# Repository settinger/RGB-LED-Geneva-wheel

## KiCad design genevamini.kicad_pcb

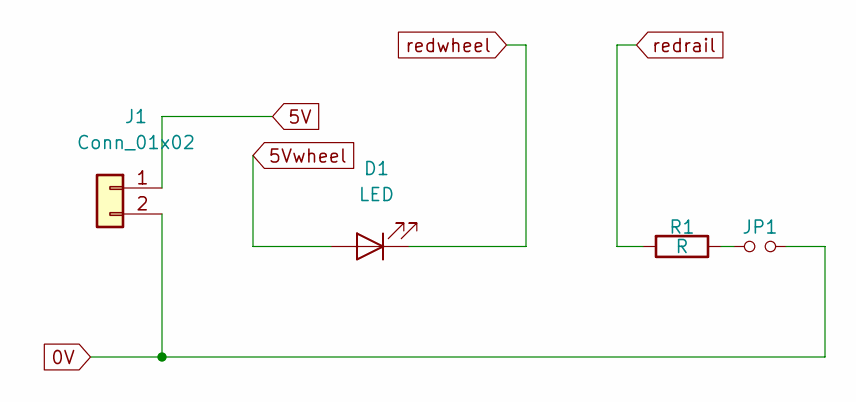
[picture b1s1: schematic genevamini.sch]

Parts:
D1: LED; LED_D3.0mm
J1: Conn_01x02; BatteryHolder_Keystone_1058_1x2032
JP1: Jumper_NO_Small; jumper
R1: R; R_Axial_DIN0204_L3.6mm_D1.6mm_P7.62mm_Horizontal

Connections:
0V: J1.2, JP1.2
5V: J1.1
5Vwheel: D1.2 (A)
unnamed: JP1.1, R1.1
redrail: R1.2
redwheel: D1.1 (K)

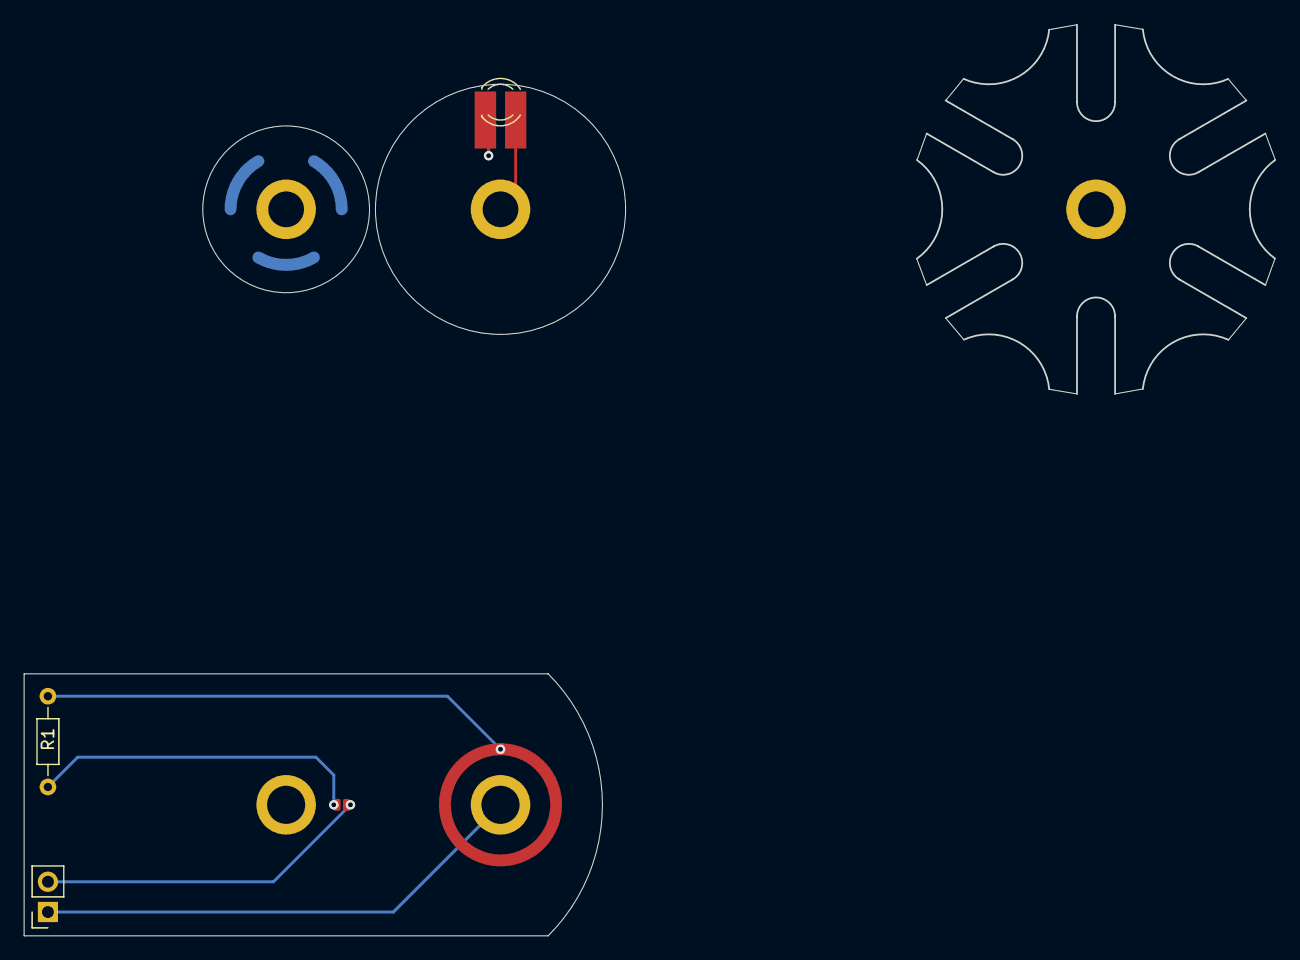
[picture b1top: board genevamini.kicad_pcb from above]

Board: 2 copper layers, 105.1 x 76.5 mm, 4 parts (0 on the bottom side), 2 nets.

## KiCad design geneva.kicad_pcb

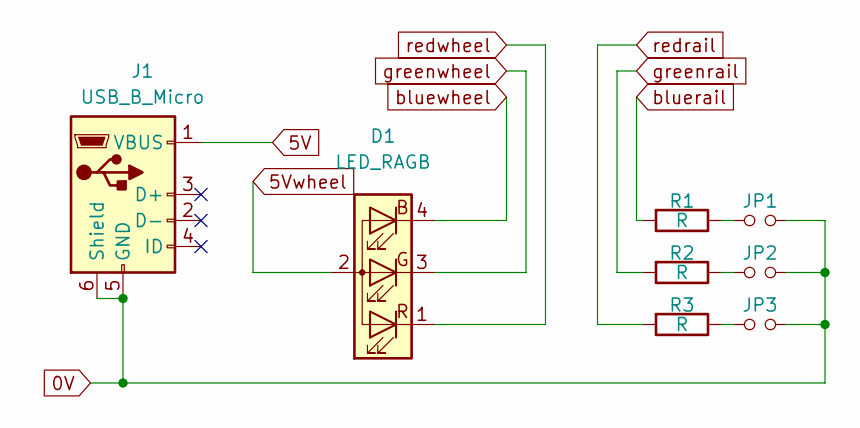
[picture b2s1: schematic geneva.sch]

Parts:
D1: LED_RAGB; LED_D5.0mm-4_RGB
J1: USB_B_Micro; USB_Micro-B_GCT_USB3076-30-A
JP1, JP2, JP3: Jumper_NO_Small; jumper
R1, R2, R3: R; R_Axial_DIN0204_L3.6mm_D1.6mm_P7.62mm_Horizontal

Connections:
0V: J1.5 (GND), J1.6 (Shield), JP1.2, JP2.2, JP3.2
5V: J1.1 (VBUS)
5Vwheel: D1.2 (A)
unnamed: JP1.1, R1.1
unnamed: JP2.1, R2.1
unnamed: JP3.1, R3.1
bluerail: R1.2
bluewheel: D1.4 (BK)
greenrail: R2.2
greenwheel: D1.3 (GK)
redrail: R3.2
redwheel: D1.1 (RK)

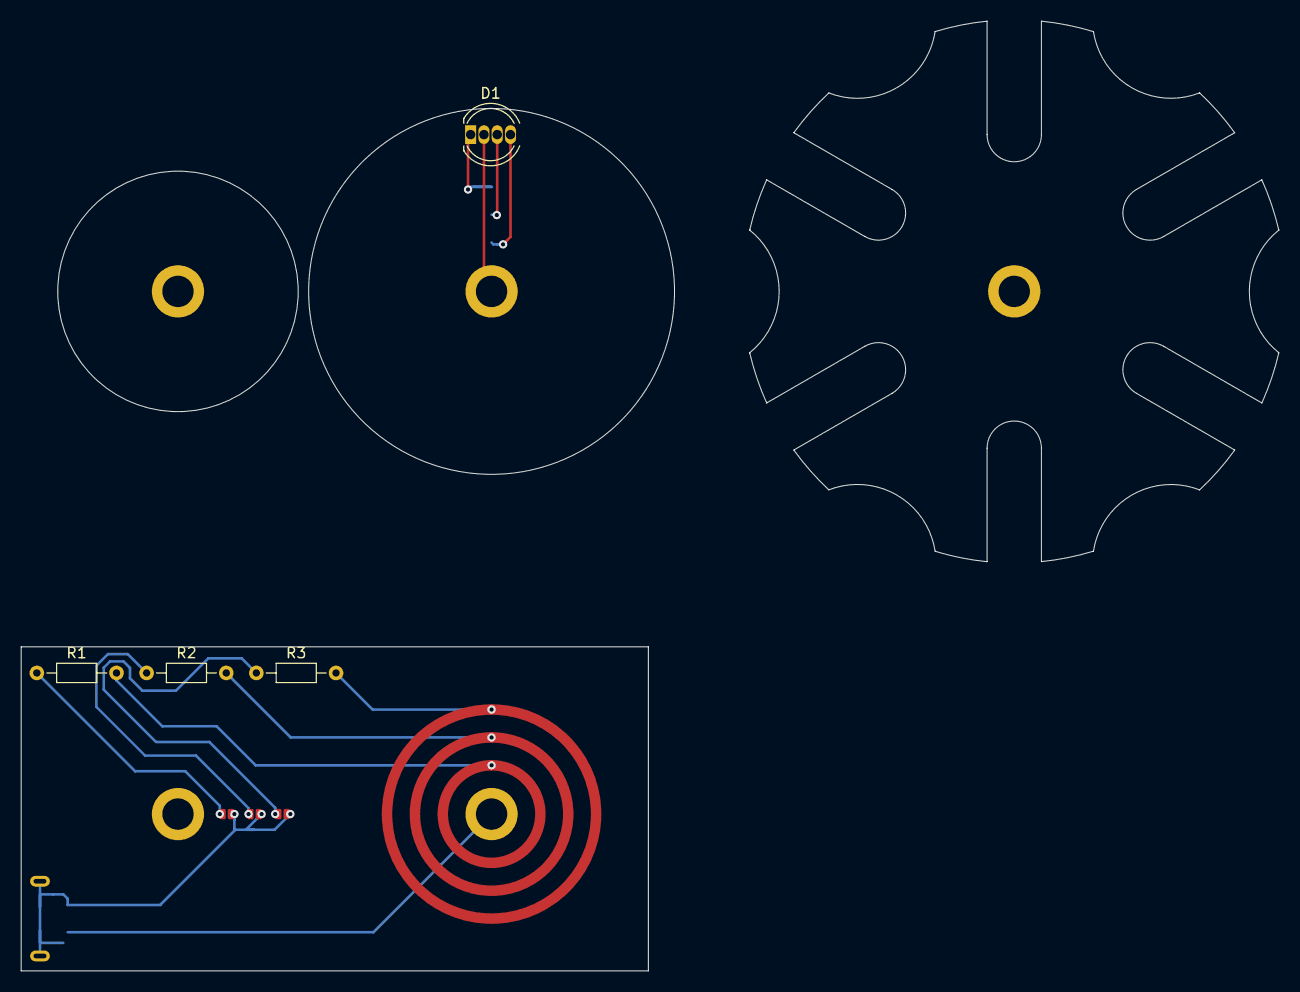
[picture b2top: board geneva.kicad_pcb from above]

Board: 2 copper layers, 120.3 x 90.8 mm, 8 parts (1 on the bottom side), 4 nets.

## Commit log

2020-01-14 A ridiculous idea to make an RGB LED geneva wheel
2020-01-15 Added gerbers
2020-01-15 Updated nets
2020-02-13 Added mini version to repo
2020-02-13 Removed old gerbers; removed soldermask from parts of minigeneva
2020-02-13 Added gif
2020-02-13 Removed soldermask layer from critical parts of RGB version
2020-02-17 Added gitignore
2020-02-17 Various changes to mini version, going to order it with 2oz copper
2020-02-18 Mini geneva mods
2020-02-18 Gitignore nonsense
2020-02-18 I really should have put a gitignore in here sooner
